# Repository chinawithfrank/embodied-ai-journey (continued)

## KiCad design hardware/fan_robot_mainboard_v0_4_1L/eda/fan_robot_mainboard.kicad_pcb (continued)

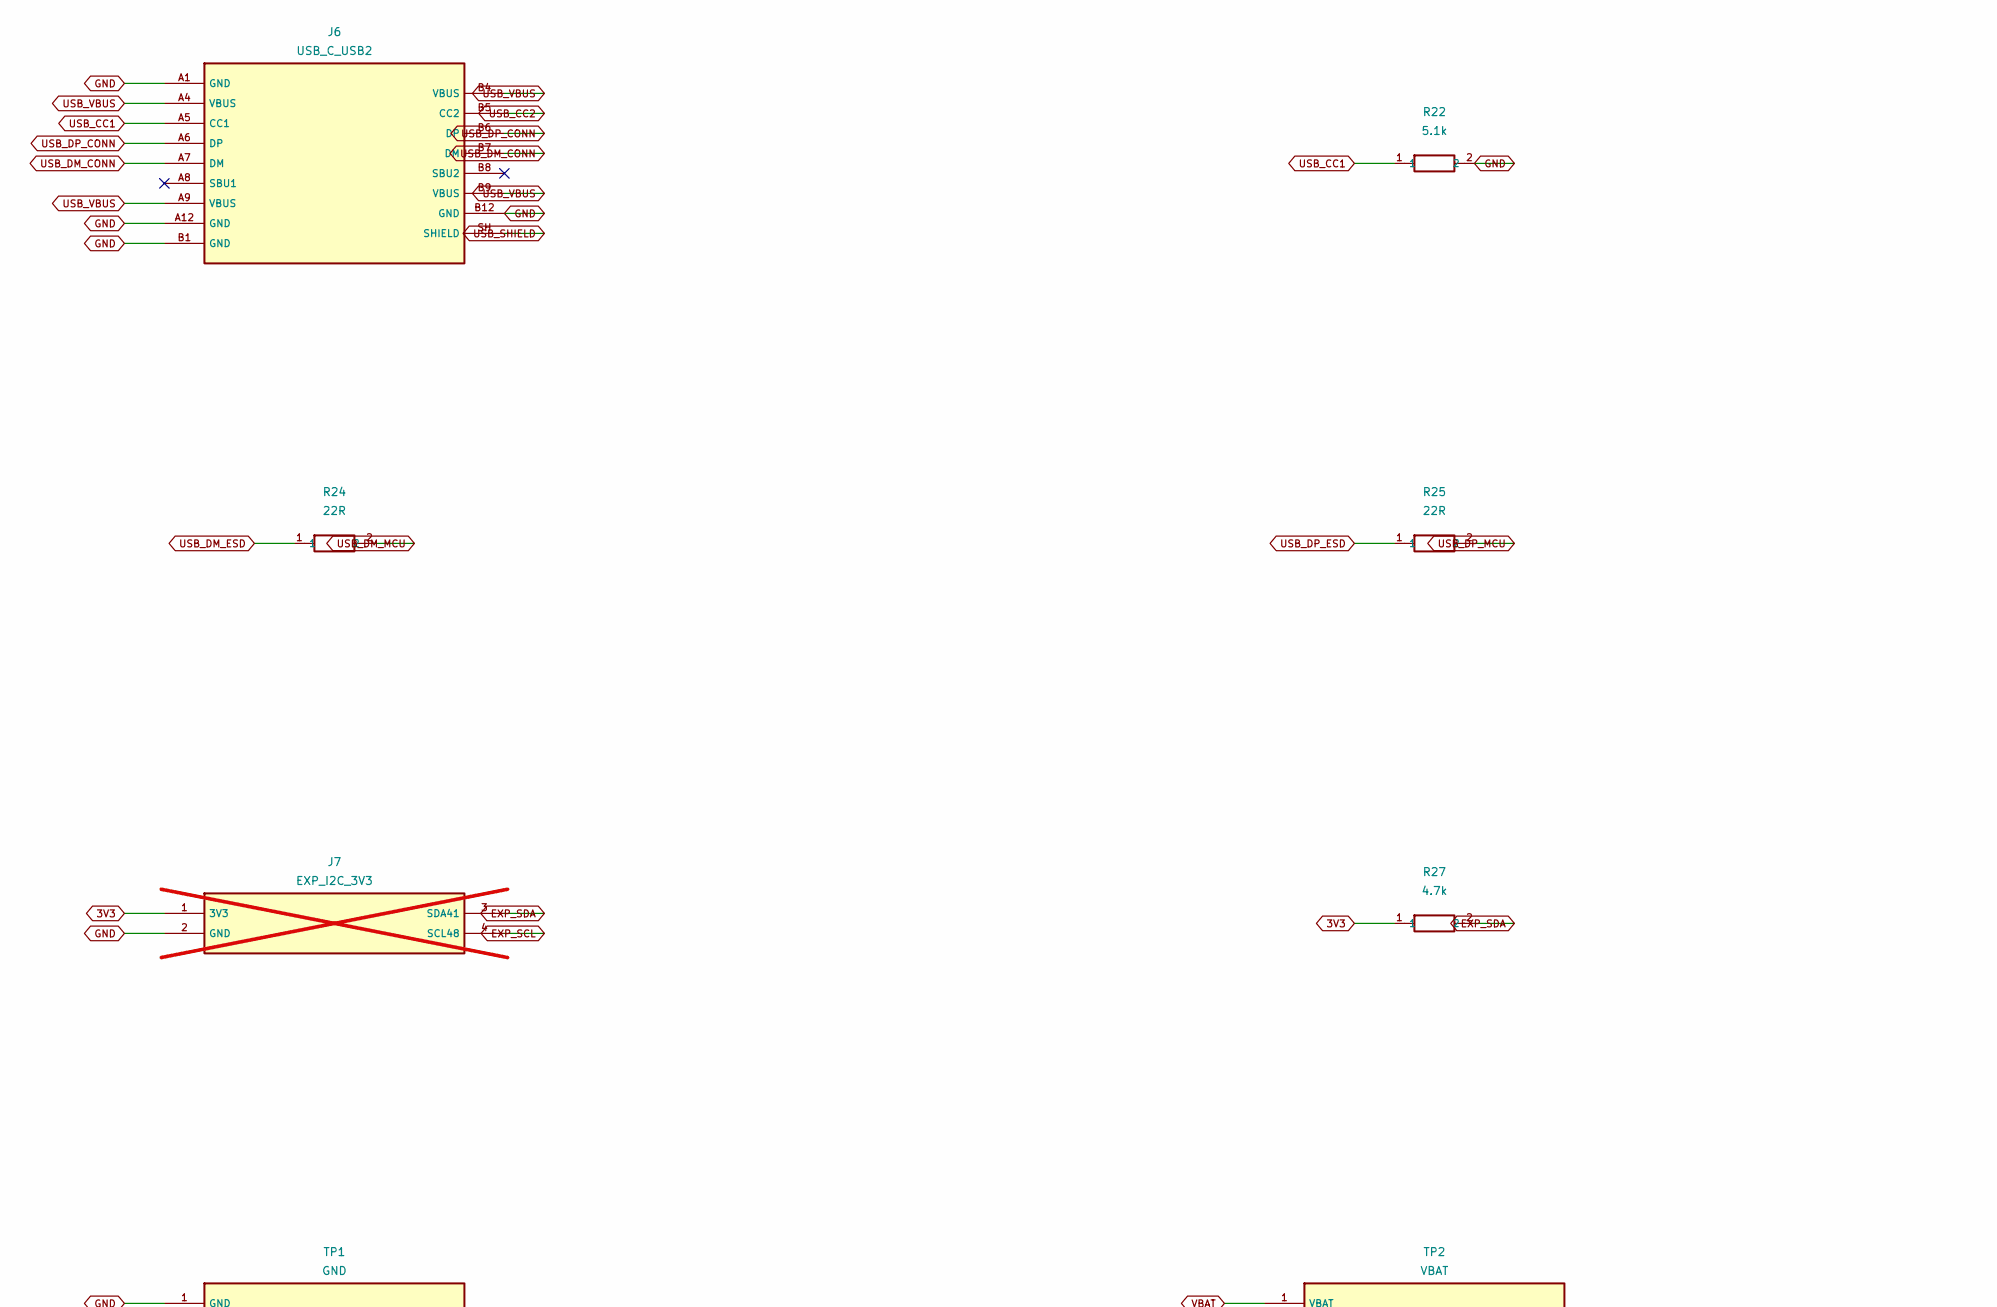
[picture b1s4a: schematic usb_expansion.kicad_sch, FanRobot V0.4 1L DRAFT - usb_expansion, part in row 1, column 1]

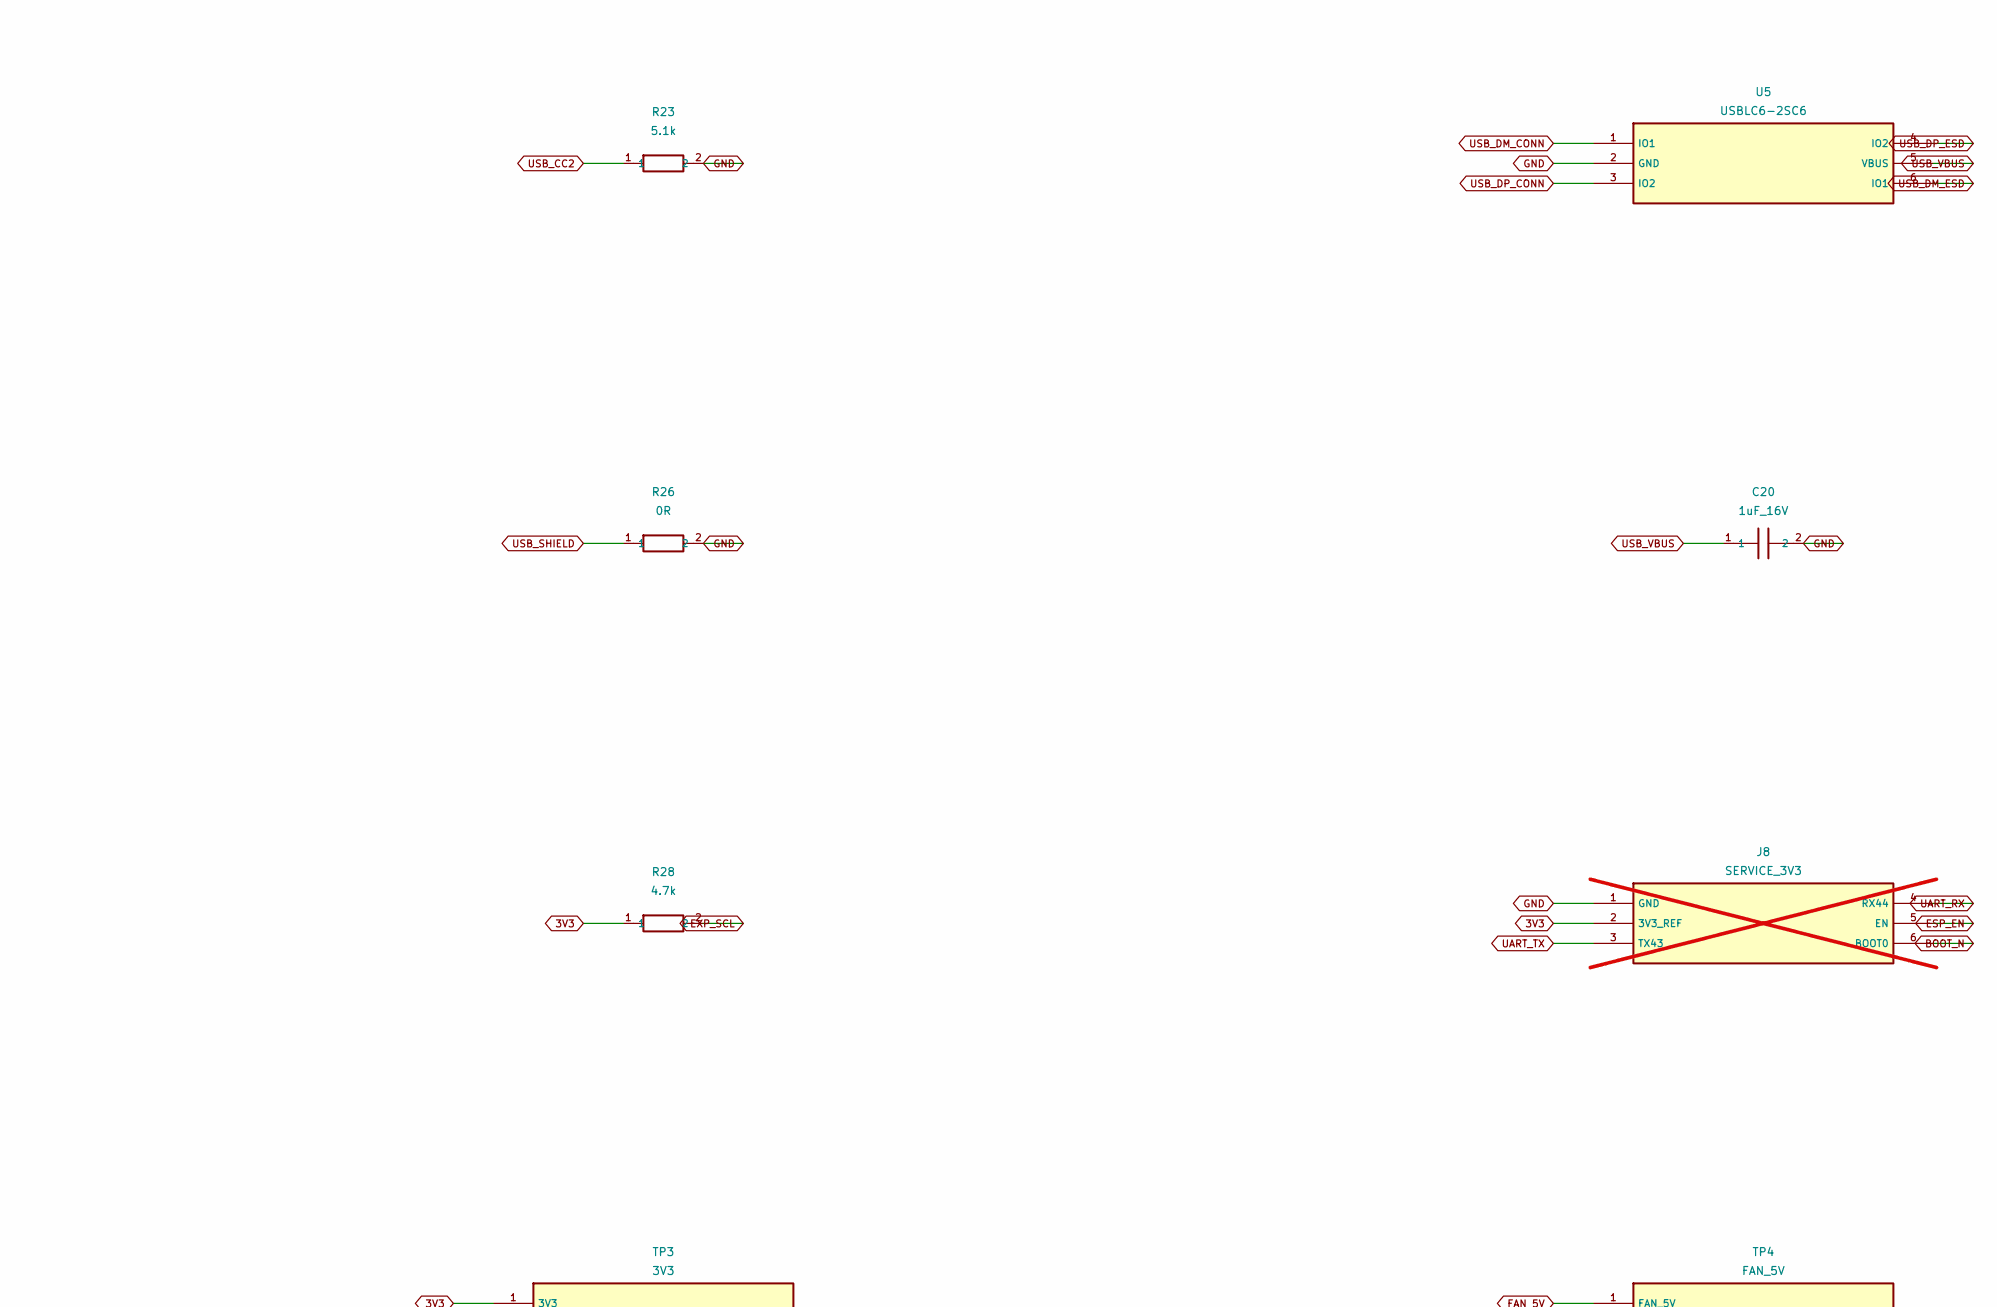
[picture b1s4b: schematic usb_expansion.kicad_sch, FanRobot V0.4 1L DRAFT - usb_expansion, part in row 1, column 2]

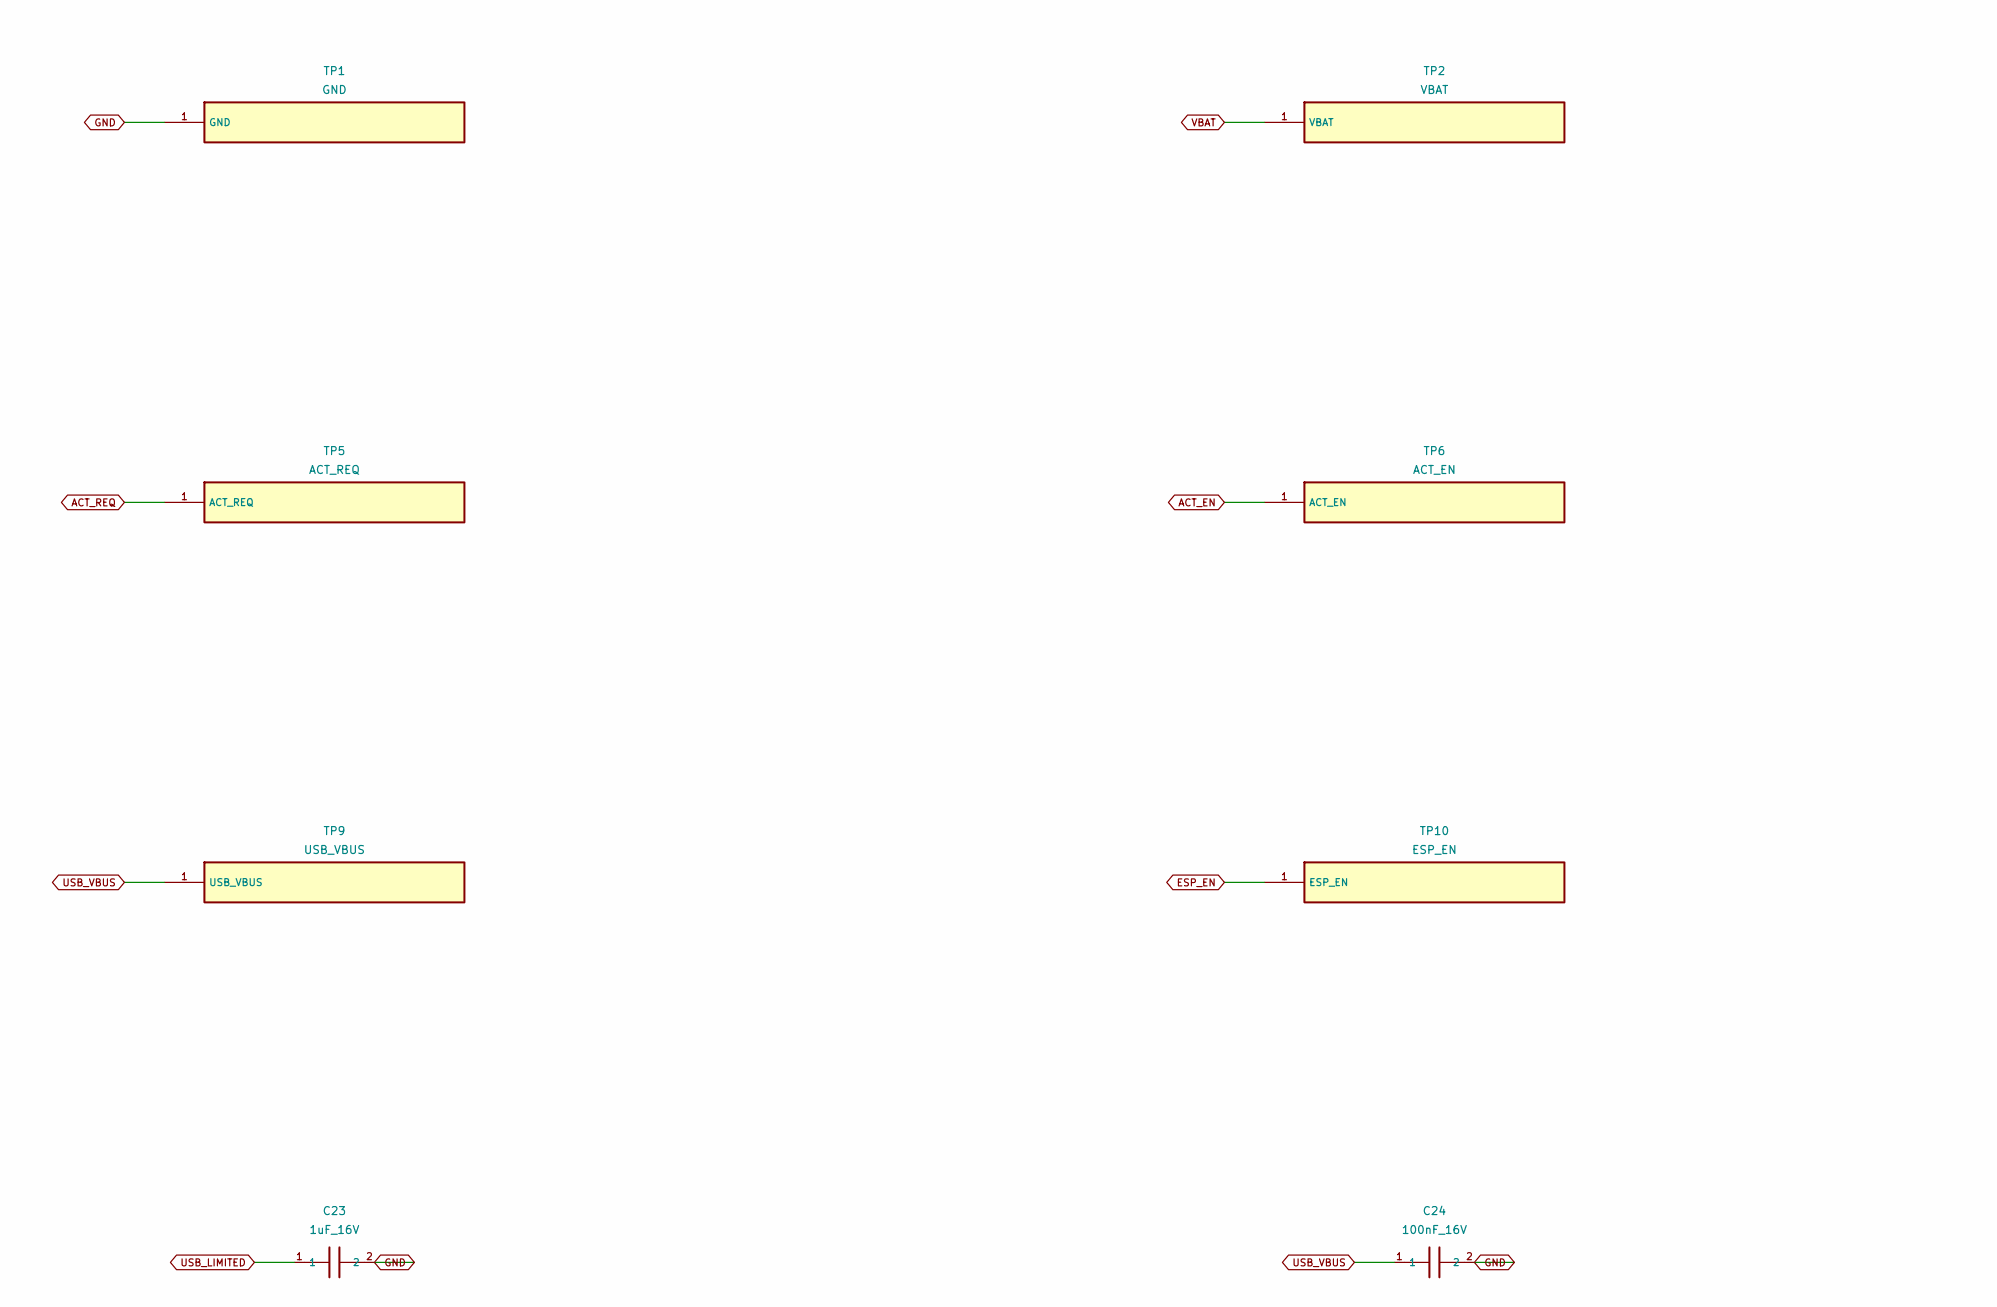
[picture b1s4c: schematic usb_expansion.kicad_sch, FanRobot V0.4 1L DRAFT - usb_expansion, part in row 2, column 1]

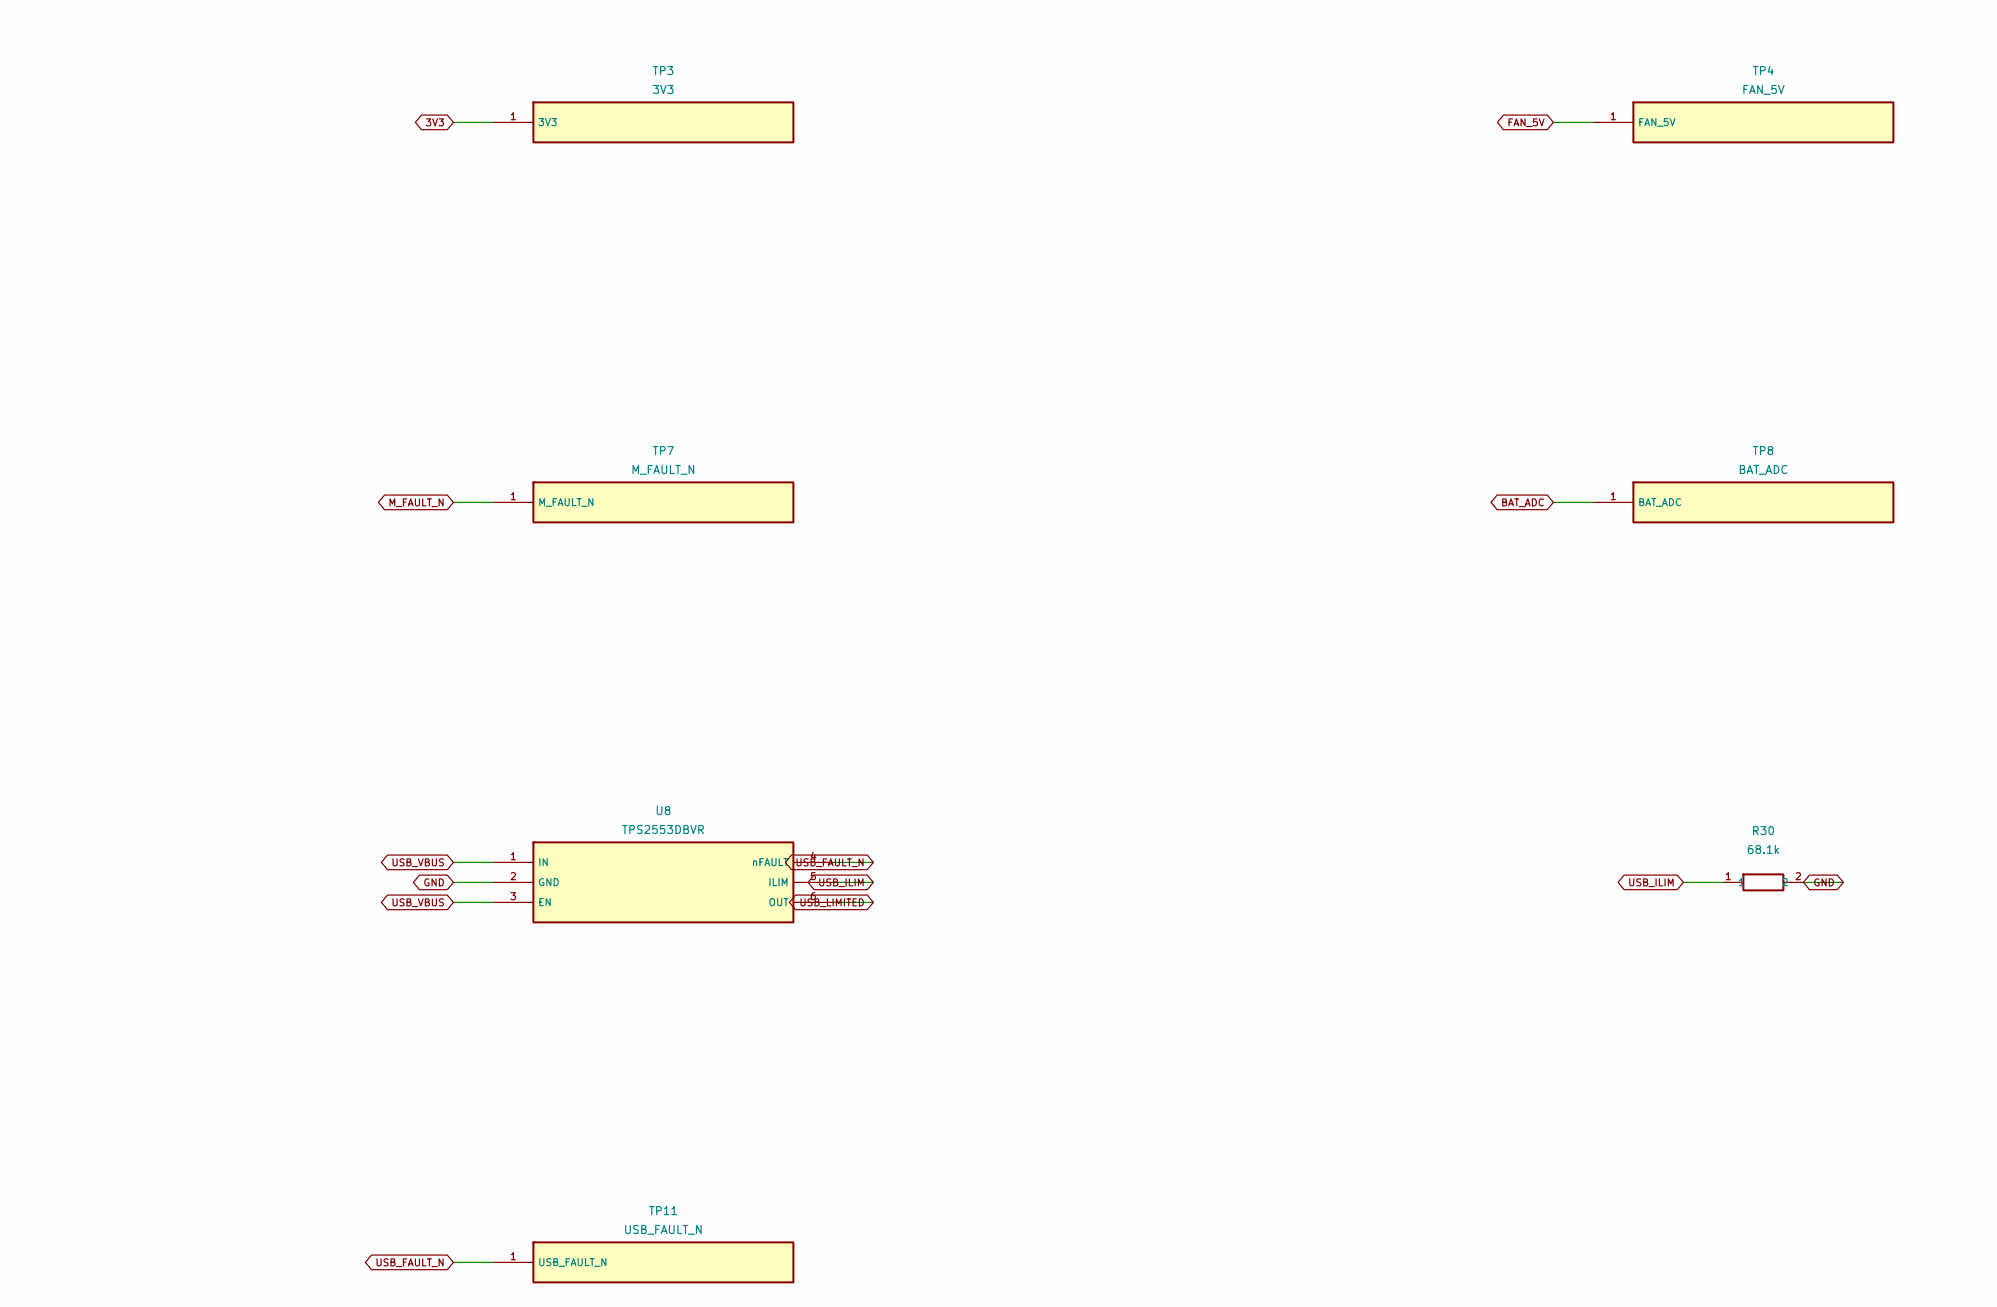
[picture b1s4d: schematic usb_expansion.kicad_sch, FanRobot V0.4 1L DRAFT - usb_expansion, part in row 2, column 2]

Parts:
C20, C23: 1uF_16V; C_0805_2012Metric; MPN GRM21BR71C105KA01L; LCSC C77079
C24: 100nF_16V; C_0603_1608Metric; MPN GRM188R71C104KA01D; LCSC C45000
J6: USB_C_USB2; USB_C_Receptacle_HRO_TYPE-C-31-M-12; MPN TYPE-C-31-M-12; LCSC C165948
J7: EXP_I2C_3V3; PinHeader_1x04_P2.54mm_Vertical; MPN DNP_2.54mm_1x4; not fitted
J8: SERVICE_3V3; PinHeader_1x06_P2.54mm_Vertical; MPN DNP_2.54mm_1x6; not fitted
R22, R23: 5.1k; R_0603_1608Metric; MPN 0603WAF5101T5E; LCSC C23186
R24, R25: 22R; R_0603_1608Metric; MPN 0603WAF220JT5E; LCSC C23345
R26: 0R; R_0603_1608Metric; MPN 0603WAF0000T5E; LCSC C21189
R27, R28: 4.7k; R_0603_1608Metric; MPN 0603WAF4701T5E; LCSC C23162
R30: 68.1k; R_0603_1608Metric; MPN 0603WAF6812T5E; LCSC C25976
TP1: GND; TestPoint_Pad_D1.0mm
TP2: VBAT; TestPoint_Pad_D1.0mm
TP3: 3V3; TestPoint_Pad_D1.0mm
TP4: FAN_5V; TestPoint_Pad_D1.0mm
TP5: ACT_REQ; TestPoint_Pad_D1.0mm
TP6: ACT_EN; TestPoint_Pad_D1.0mm
TP7: M_FAULT_N; TestPoint_Pad_D1.0mm
TP8: BAT_ADC; TestPoint_Pad_D1.0mm
TP9: USB_VBUS; TestPoint_Pad_D1.0mm
TP10: ESP_EN; TestPoint_Pad_D1.0mm
TP11: USB_FAULT_N; TestPoint_Pad_D1.0mm
U5: USBLC6-2SC6; SOT-23-6; MPN USBLC6-2SC6; LCSC C7519
U8: TPS2553DBVR; SOT-23-6; MPN TPS2553DBVR; LCSC C55266

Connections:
3V3: J7.1 (3V3), J8.2 (3V3_REF), R27.1, R28.1, TP3.1; also elsewhere on the board
ACT_EN: TP6.1; also elsewhere on the board
ACT_REQ: TP5.1; also elsewhere on the board
BAT_ADC: TP8.1; also elsewhere on the board
BOOT_N: J8.6 (BOOT0); also elsewhere on the board
ESP_EN: J8.5 (EN), TP10.1; also elsewhere on the board
EXP_SCL: J7.4 (SCL48), R28.2; also elsewhere on the board
EXP_SDA: J7.3 (SDA41), R27.2; also elsewhere on the board
FAN_5V: TP4.1; also elsewhere on the board
GND: C20.2, C23.2, C24.2, J6.A1 (GND), J6.A12 (GND), J6.B1 (GND), J6.B12 (GND), J7.2 (GND), J8.1 (GND), R22.2, R23.2, R26.2, R30.2, TP1.1, U5.2 (GND), U8.2 (GND); also elsewhere on the board
M_FAULT_N: TP7.1; also elsewhere on the board
UART_RX: J8.4 (RX44); also elsewhere on the board
UART_TX: J8.3 (TX43); also elsewhere on the board
USB_CC1: J6.A5 (CC1), R22.1
USB_CC2: J6.B5 (CC2), R23.1
USB_DM_CONN: J6.A7 (DM), J6.B7 (DM), U5.1 (IO1)
USB_DM_ESD: R24.1, U5.6 (IO1)
USB_DM_MCU: R24.2; also elsewhere on the board
USB_DP_CONN: J6.A6 (DP), J6.B6 (DP), U5.3 (IO2)
USB_DP_ESD: R25.1, U5.4 (IO2)
USB_DP_MCU: R25.2; also elsewhere on the board
USB_FAULT_N: TP11.1, U8.4 (nFAULT)
USB_ILIM: R30.1, U8.5 (ILIM)
USB_LIMITED: C23.1, U8.6 (OUT); also elsewhere on the board
USB_SHIELD: J6.SH (SHIELD), R26.1
USB_VBUS: C20.1, C24.1, J6.A4 (VBUS), J6.A9 (VBUS), J6.B4 (VBUS), J6.B9 (VBUS), TP9.1, U5.5 (VBUS), U8.1 (IN), U8.3 (EN)
VBAT: TP2.1; also elsewhere on the board

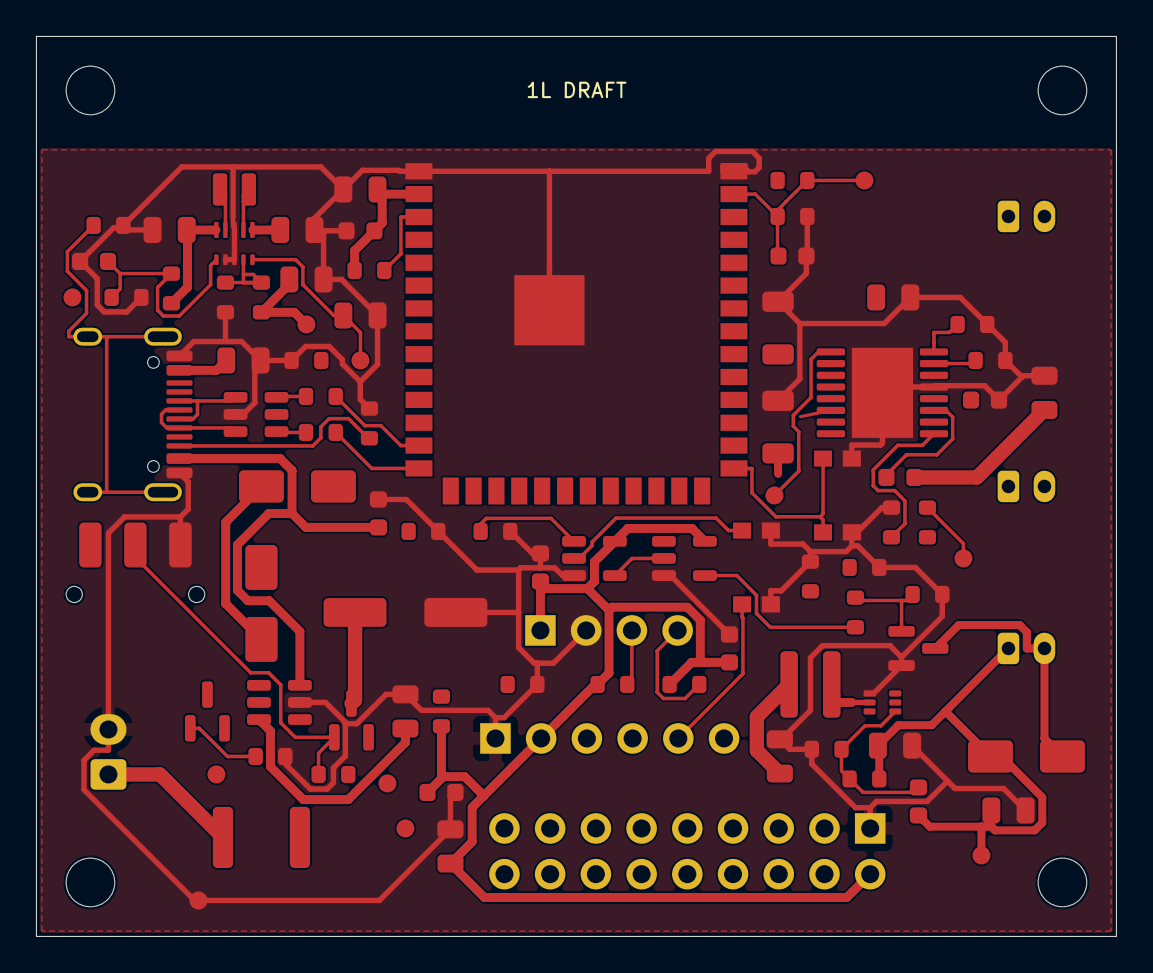
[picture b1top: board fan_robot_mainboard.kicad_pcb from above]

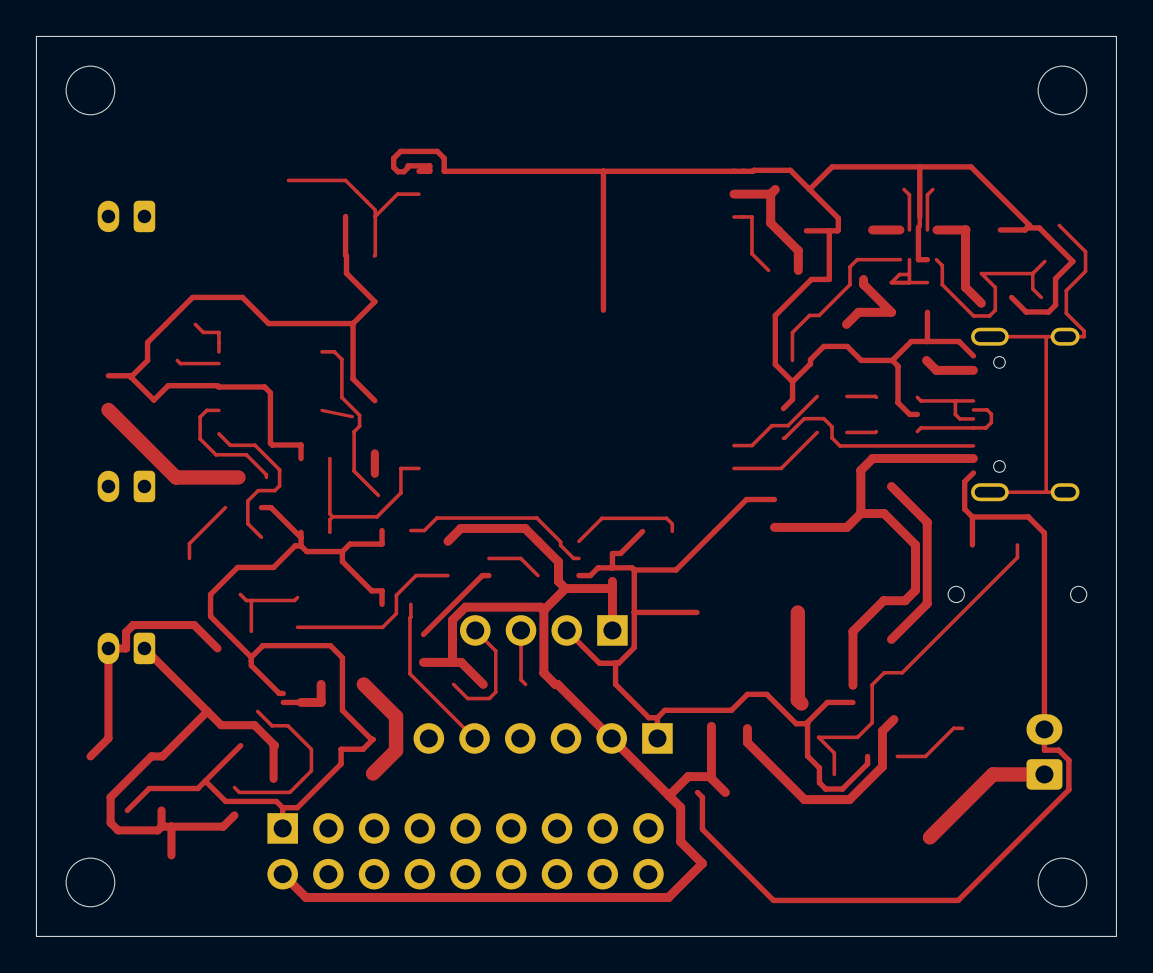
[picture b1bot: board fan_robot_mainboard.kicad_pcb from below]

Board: 2 copper layers, 60.0 x 50.0 mm, 99 parts (7 on the bottom side), 70 nets.

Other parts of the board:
H1, H2, H3, H4: MountingHole_2.7mm_M2.5

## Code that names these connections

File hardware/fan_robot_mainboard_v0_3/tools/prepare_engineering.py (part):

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def new(ref,value,pins,section='power',package='0603'):
 p[ref]=dict(ref=ref,value=value,package=package,pins={str(k):dict(name=v[0],net=v[1]) for k,v in pins.items()},section=section,mpn='',manufacturer='',note='',status='DRAFT')
# MOSFET power control: slide-switch contacts carry only gate current.
p['F1']['pins']['1']['net']='BAT_RAW'
p['Q2']['pins']['2']['net']='BAT_PROTECTED'
new('Q3','AO3401A',{1:('G','POWER_GATE'),2:('S','BAT_PROTECTED'),3:('D','VBAT')},package='SOT-23')
new('R29','100k',{1:('1','POWER_GATE'),2:('2','BAT_PROTECTED')})
p['SW1']['pins']={'1':dict(name='OFF',net=None),'2':dict(name='COMMON',net='POWER_GATE'),'3':dict(name='ON',net='GND')}
p['SW1']['value']='POWER_GATE_SWITCH'
# ADC1 is usable while Wi-Fi runs. This is a separate new-board pin map.
p['U1']['pins']['8']['net']='M_AIN1' # IO15
p['U1']['pins']['39']['net']='BAT_ADC' # IO1/ADC1_CH0
p['U1']['note']='N16R8: 16MB Flash, 8MB Octal PSRAM. GPIO35/36/37 NC. New board: BAT_ADC GPIO1/ADC1; AIN1 GPIO15. Other mappings preserved.'
p['C13']['note']='ADC1/GPIO1 channel 0; calibrate 1M/330k divider and use settled averaged oneshot reads. No ADC2/Wi-Fi contention.'
# Limit USB logic supply independently of battery-only actuator feed.
new('U8','TPS2553DBVR',{1:('IN','USB_VBUS'),2:('GND','GND'),3:('EN','USB_VBUS'),4:('nFAULT','USB_FAULT_N'),5:('ILIM','USB_ILIM'),6:('OUT','USB_LIMITED')},'usb','SOT-23-6')
new('R30','68.1k',{1:('1','USB_ILIM'),2:('2','GND')},'usb')
new('C23','1uF_16V',{1:('1','USB_LIMITED'),2:('2','GND')},'usb','0805')
new('C24','100nF_16V',{1:('1','USB_VBUS'),2:('2','GND')},'usb')
p['D3']['pins']['2']['net']='USB_LIMITED'
# KiCad10 HRO footprint uses SH for all four shield tabs.
new('TP11','USB_FAULT_N',{1:('USB_FAULT_N','USB_FAULT_N')},'test','TESTPAD_1MM')
ics={
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d.update(project='FanRobot_Mainboard',revision='0.3-engineering',release='IN_DESIGN_NOT_FOR_FABRICATION',parts=list(p.values()))
d['hardware_inputs']['motors']['current_limit_status']='0.39ohm,0.5W fixed engineering prototype selection; loaded start/thermal qualification after fabrication'
d['hardware_inputs']['camera']['connector_mpn']='BOOMELE 2.54-2*9P / C71956'
d['hardware_inputs']['new_board_gpio_changes']={'BAT_ADC':'GPIO1/ADC1_CH0','M_AIN1':'GPIO15','ACT_REQ':'GPIO47','M_FAULT_N':'GPIO42'}
(ROOT/'design/circuit.json').write_text(json.dumps(d,indent=2,ensure_ascii=False)+'\n')
fpdir=ROOT/'eda/FanRobot.pretty';fpdir.mkdir(exist_ok=True)
provenance=[]
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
